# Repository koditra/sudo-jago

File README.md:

# sudo jago

sudo jago is a custom alarm clock built around the XIAO ESP32-C3.

It has a custom PCB, 3D printed case, ST7789 display, buzzer, and a 3x3 button matrix.

## Features

- Custom PCB
- Custom 3D printed case
- ST7789 TFT display
- 3x3 button matrix
- Built-in buzzer
- Creates its own Wi-Fi network
- Web portal for setting the time and alarm
- Button sequence required to stop the alarm

## Schematic

## PCB

## PCB Render

## 3D Case

## Full Assembly

## Hardware

- Seeed Studio XIAO ESP32-C3
- ST7789 TFT
- 9 buttons
- Buzzer
- Custom PCB
- 3D printed enclosure

## BOM

| Quantity | Part |
|---:|---|
| 1 | Seeed Studio XIAO ESP32-C3 |
| 1 | 2.25" ST7789 TFT display |
| 9 | MX-style mechanical switches |
| 9 | 1N4148 diodes |
| 1 | 3.3V piezo buzzer |
| 1 | 8-pin 2.54mm header |
| 8 | M3x5x4 heat-set inserts |
| 4 | M3x8mm screws |
| 4 | M3x16mm screws |
| 1 | Custom PCB |
| 1 | 3D printed case |

## Firmware

The ESP32 creates its own Wi-Fi network called `sudo jago`.

Connect to it and use the web portal to set the clock and alarm. The phone can then disconnect and sudo jago runs by itself.

When the alarm goes off, a random sequence appears on the display. The physical buttons must be pressed in the correct order to stop the alarm.

## Built By

Aashvik Goel (with blare.hackclub.com tutorial to help me out)

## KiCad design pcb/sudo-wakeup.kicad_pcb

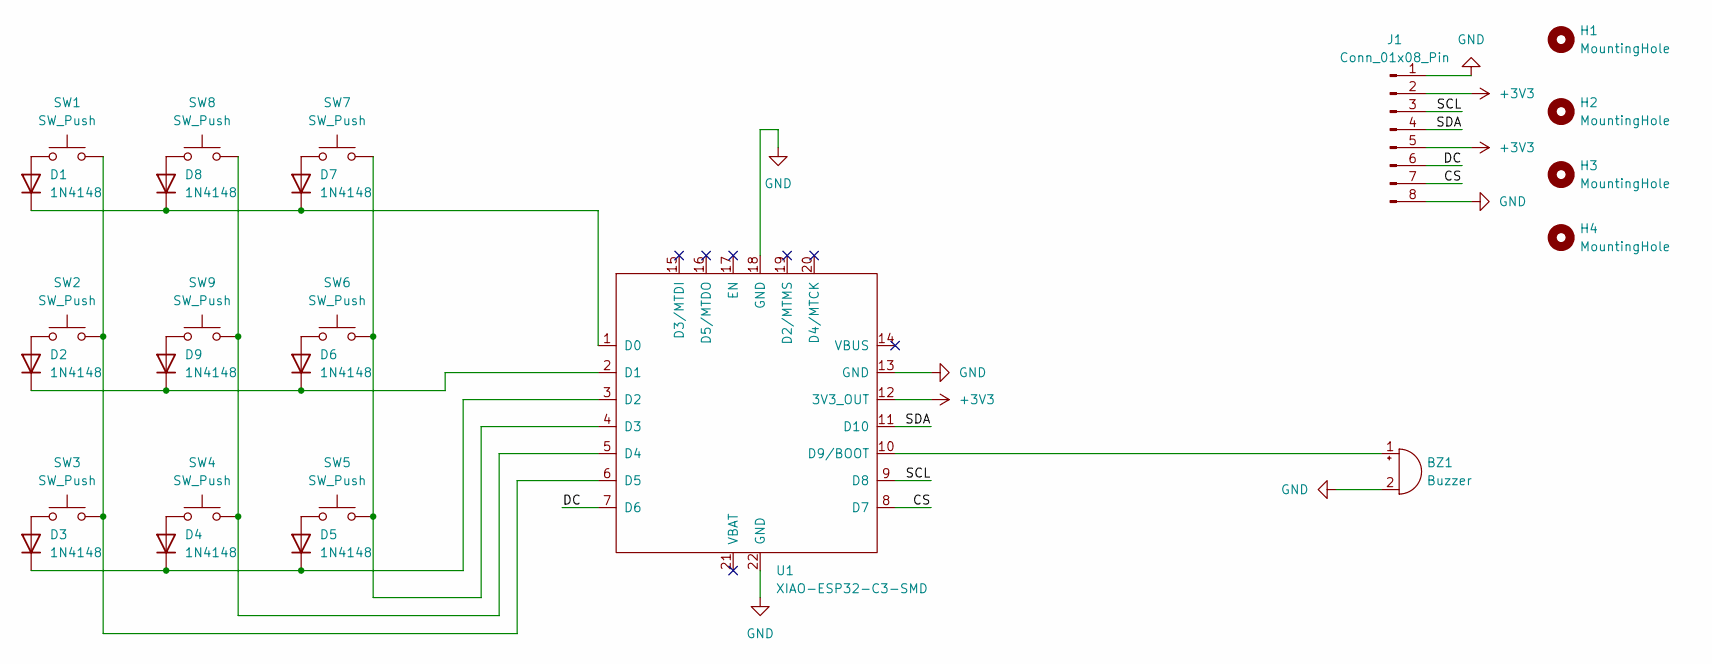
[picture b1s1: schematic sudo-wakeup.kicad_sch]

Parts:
BZ1: Buzzer; Buzzer_12x9.5RM7.6
D1, D2, D3, D4, D5, D6, D7, D8, D9: 1N4148; D_DO-35_SOD27_P7.62mm_Horizontal
H1, H2, H3, H4: MountingHole; MountingHole_3.2mm_M3
J1: Conn_01x08_Pin; PinSocket_1x08_P2.54mm_Vertical
SW1, SW2, SW3, SW4, SW5, SW6, SW7, SW8, SW9: SW_Push; SW_Cherry_MX_1.00u_PCB
U1: XIAO-ESP32-C3-SMD; XIAO-ESP32-C3-DIP

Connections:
+3V3: J1.2, J1.5, U1.12 (3V3_OUT)
/CS: J1.7, U1.8 (D7)
/DC: J1.6, U1.7 (D6)
/SCL: J1.3, U1.9 (D8)
/SDA: J1.4, U1.11 (D10)
GND: BZ1.2 (-), J1.1, J1.8, U1.13 (GND), U1.18 (GND), U1.22 (GND)
unnamed: BZ1.1 (+), U1.10 (D9/BOOT)
unnamed: D1.2 (A), SW1.1
unnamed: D1.1 (K), D7.1 (K), D8.1 (K), U1.1 (D0)
unnamed: D2.2 (A), SW2.1
unnamed: D2.1 (K), D6.1 (K), D9.1 (K), U1.2 (D1)
unnamed: D3.2 (A), SW3.1
unnamed: D3.1 (K), D4.1 (K), D5.1 (K), U1.3 (D2)
unnamed: D4.2 (A), SW4.1
unnamed: D5.2 (A), SW5.1
unnamed: D6.2 (A), SW6.1
unnamed: D7.2 (A), SW7.1
unnamed: D8.2 (A), SW8.1
unnamed: D9.2 (A), SW9.1
unnamed: SW5.2, SW6.2, SW7.2, U1.4 (D3)
unnamed: SW4.2, SW8.2, SW9.2, U1.5 (D4)
unnamed: SW1.2, SW2.2, SW3.2, U1.6 (D5)

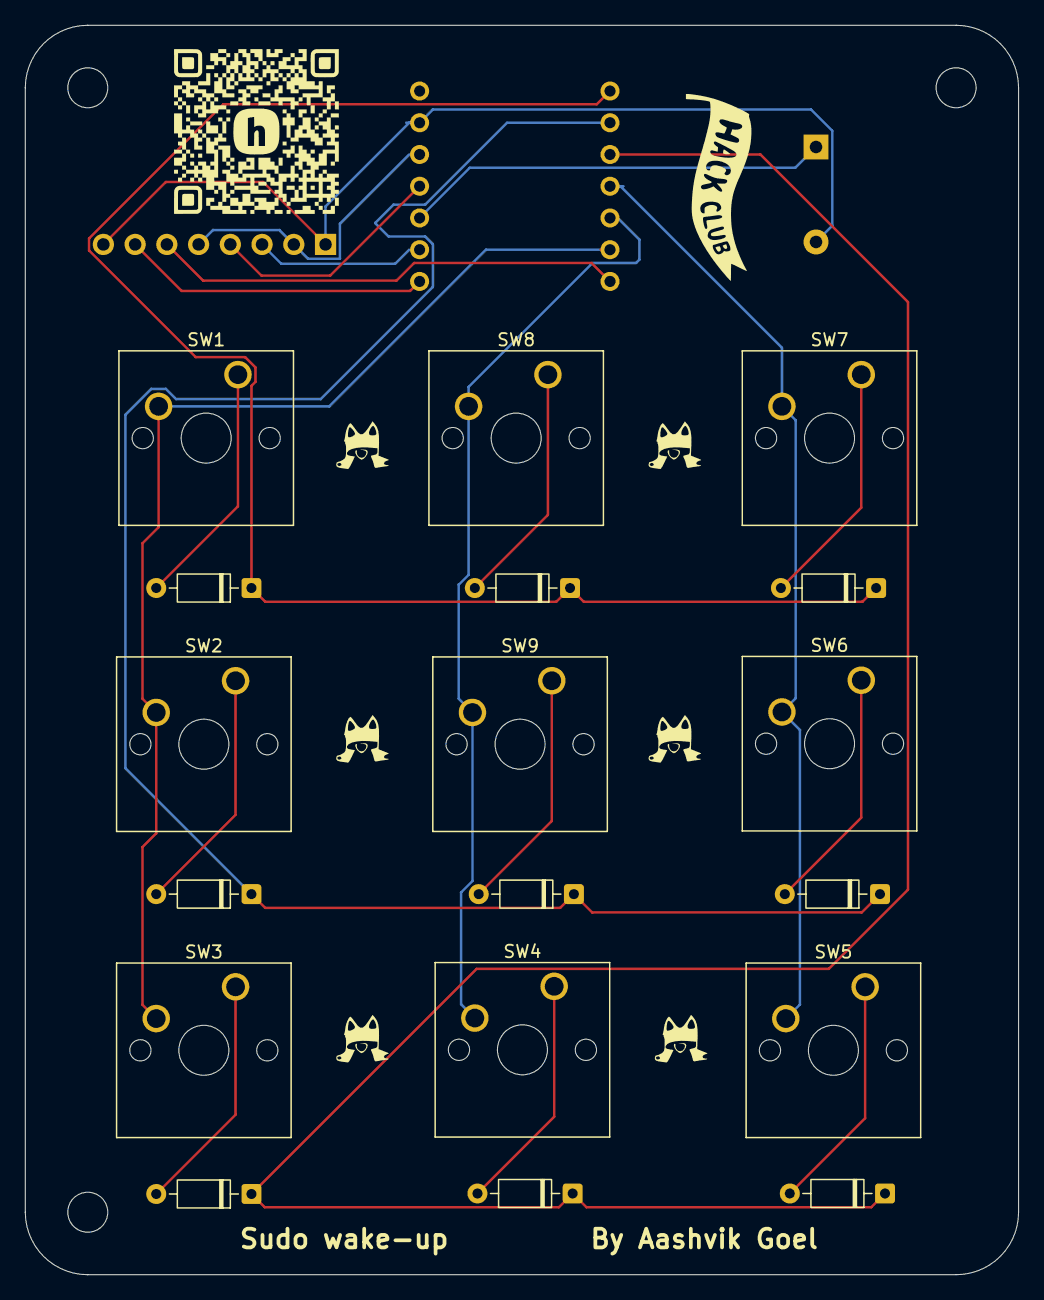
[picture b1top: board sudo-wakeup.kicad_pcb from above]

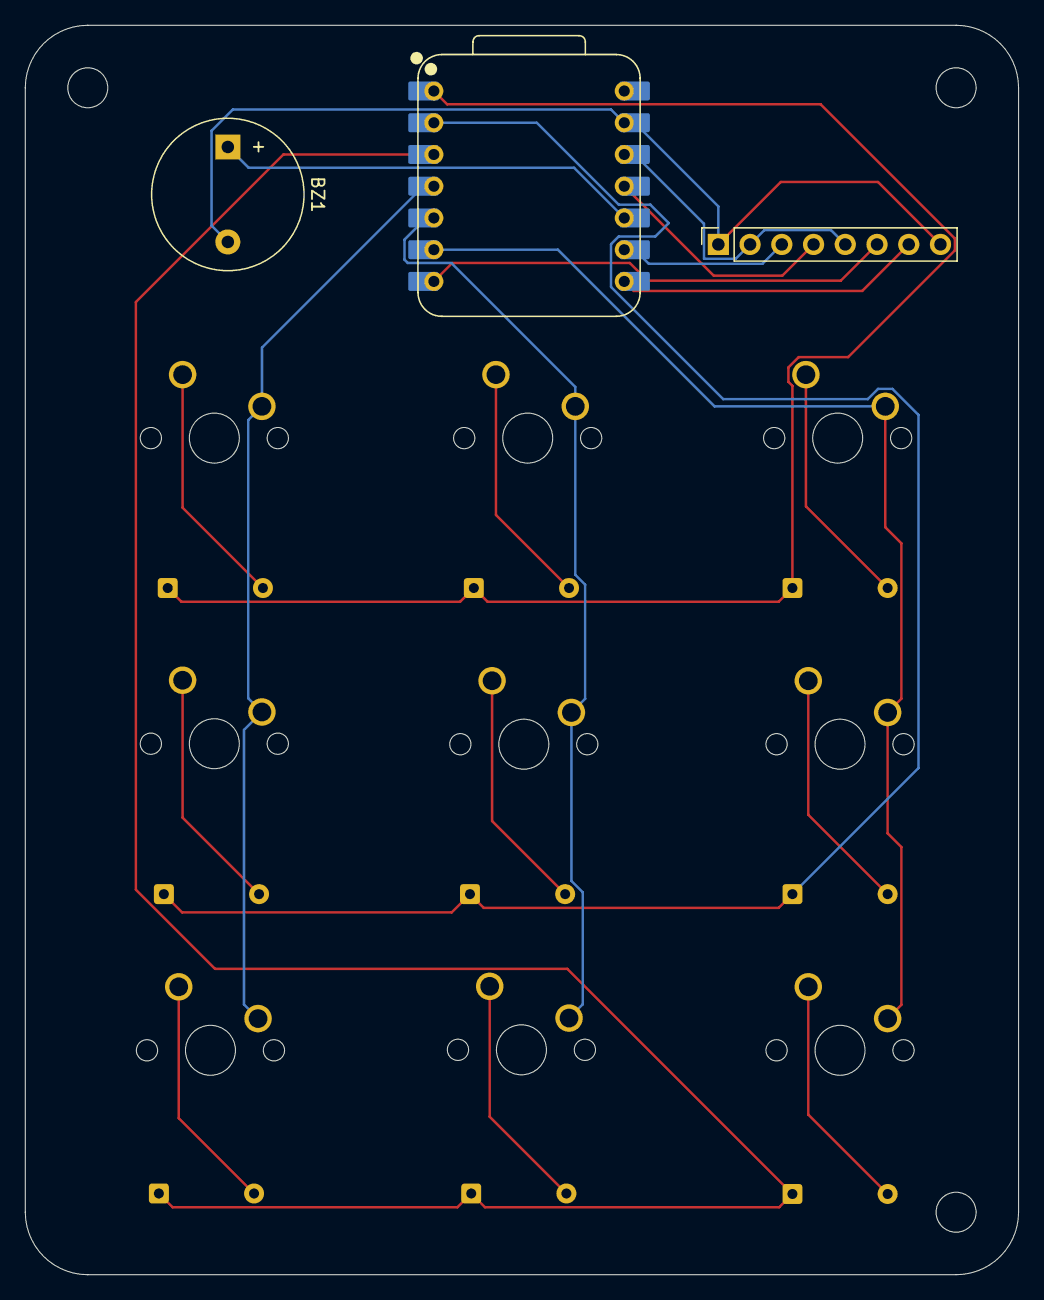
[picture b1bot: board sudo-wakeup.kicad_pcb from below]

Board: 2 copper layers, 79.5 x 100.0 mm, 24 parts (3 on the bottom side), 22 nets.
